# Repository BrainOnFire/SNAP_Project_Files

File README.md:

# S.N.A.P. Version 6.0

</a>

Soil Nutrient Analysis Prototype or S.N.A.P. for short, is an agricultural device that allows farmers to know the best type of nutrient present in a soil sample. The most common types of nutrients found in the ground are Nitrogen, Phosphorus, and Potassium. Photo-sensing sensors can observe these nutrients when an infrared beam hits a sample. Having this information in less than 10 minutes allows the farmer to decide which crop to plant in the selected soil, saving a lot of time and money. The device has come a long way, as this is the sixth iteration of the project. SNAP 6.0 is a BLE, Low-Power, feature-rich sensing device. Here are some specs of the device:

- STM32WB35CCU7A as main MCU (Ultra-low-power dual-core ARM Cortex-M4 with FPU, Bluetooth 5.2, 256KB Flash, 32MHz)
- Integrated Lithium-Ion battery charging with MCP73831 (Charge current 500mA, 4.2V Regulation, Reverse Discharge Protection)
- Battery protection using AP9101C (overcharge voltage, over-discharge voltage, overcharge current, over-discharge current)
- Boost Converter from 3.0V to 5.2V using MT3608 (turns on/off by MCU)
- Temperature and humidity sensing using SHT31-DIS
- OLED Screen for displaying information with low consumption
- PCB Antenna with impedance matching for Bluetooth Low Energy
- USB Type-C 2.0 for 5V power supply and communication

## PCB Design
The design and development of the printed circuit board were done using KiCAD 6.0. The PCB in question is a 4-layer board with a thickness of 1.62 mm and overall dimensions of 66.80 mm x 47.34 mm. The layer stack up is Signal - Ground - Ground - Mixed. 

A USB-C Type Receptacle was used for the power supply coupled with a USBLC6-2SC6 ESD protection chip. Serial Wire is used for the programming of the STM32 chip. A MOSFET and a Schottky Diode are used in order to protect the device when both battery and USB are connected and supply power to the system. Both inputs are regulated by the ADP121 LDO which outputs a voltage of 3.0V to the MCU and to the boost-up converter. The amplification system, the three IR LEDs, the Phototransistor, the SHT31, and the OLED screen are supplied by the 5.2V outputted by the boost-up converter MT3608. Three 2N700 MOSFETs are used to control the IR LEDs through the MCU. 

A total of 27 decoupling capacitors of different values and sizes are used to filter unwanted frequencies. 

A filter PI and RF Band Pass filter are used for the 2.4GHz PCB BLE antenna. The values of capacitance and inductance were calculated using the impedance of the PCB antenna (obtained from [AN5129](https://www.st.com/resource/en/application_note/an5129-low-cost-pcb-antenna-for-24ghz-radio-meander-design-for-stm32wb-series-stmicroelectronics.pdf)), in order to obtain a matching impedance of 50 ohms. The next two images show the first and second pages of the schematic; every part of the device is clearly named.

</a>
</a>

This PCB was manufactured by JLCPCB using the controlled impedance stack up JLC04161H-7628 for a dielectric constant of 4.6. This provides a matching impedance of 50 ohm for the traces of the embedded antenna that mitigate potential power losses due to parasitic capacitances. The SMD components were soldered using an SMD reflow process with a heat gun.

</a>
</a>

Most of the components were selected for the sole purpose of low energy consumption. The battery selected was a 2500mAh LiPo battery which can be charged through the device's USB type C. With this battery capacity, the device is capable of lasting for almost 30 days without charging, while being completely on. If the device's switch is turned OFF, the battery can last for almost a year and a half without the need for charging. Using a special Fluke Ammeter the total consumption of the device in this state is 185nA. This consumption happens because the device is not completely OFF; some components of the battery's charging system and the LDO are still drawing some current. The challenge of this device's design was keeping the consumption to a minimum. The team is very satisfied with the results.

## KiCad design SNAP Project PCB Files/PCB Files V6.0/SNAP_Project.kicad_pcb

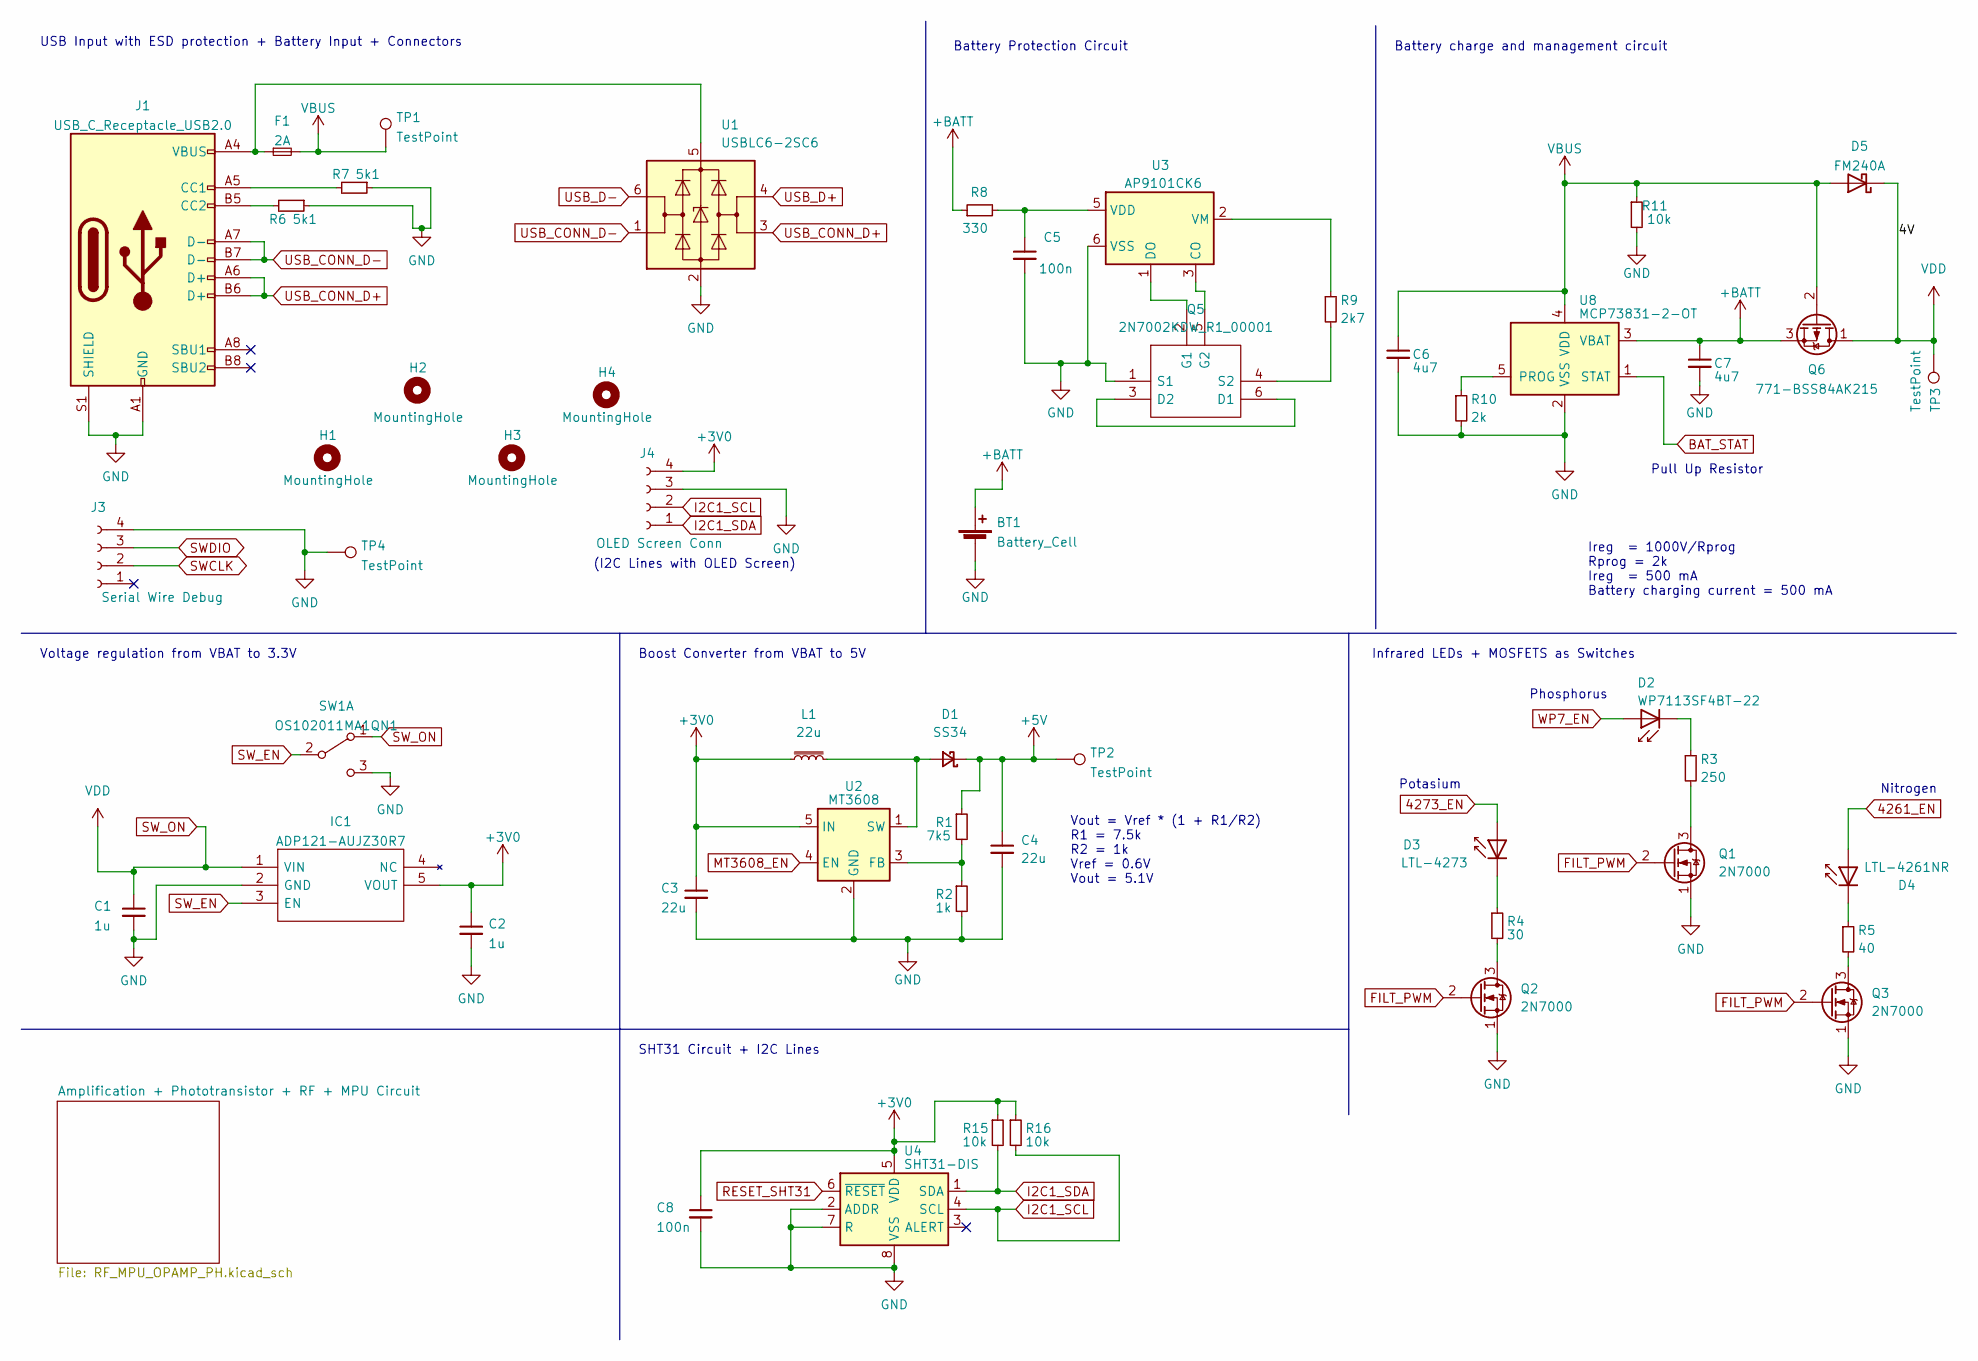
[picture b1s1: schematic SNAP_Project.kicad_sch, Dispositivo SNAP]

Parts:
BT1: Battery_Cell; Molex_KK-254_AE-6410-02A_1x02_P2.54mm_Vertical
C1, C2: 1u; C_1206_3216Metric
C3, C4: 22u; C_1206_3216Metric
C5: 100n; C_1206_3216Metric
C6, C7: 4u7; C_1206_3216Metric
C8: 100n; C_0402_1005Metric
D1: SS34; D_SMC
D2: WP7113SF4BT-22; Molex_KK-254_AE-6410-02A_1x02_P2.54mm_Vertical
D3: LTL-4273; Molex_KK-254_AE-6410-02A_1x02_P2.54mm_Vertical
D4: LTL-4261NR; Molex_KK-254_AE-6410-02A_1x02_P2.54mm_Vertical
D5: FM240A; DIOM5025X231N
F1: 2A; Fuse_0603_1608Metric; Mouser Code MFU0603FF02000P500
H1, H2, H3, H4: MountingHole; MountingHole_3mm_Pad
IC1: ADP121-AUJZ30R7; SOT95P280X100-5N; Mouser Part Number 584-ADP121-AUJZ33R7
J1: USB_C_Receptacle_USB2.0; USB_C_Receptacle_HRO_TYPE-C-31-M-12
J3: Serial Wire Debug; Molex_KK-254_AE-6410-04A_1x04_P2.54mm_Vertical
J4: OLED Screen Conn; Molex_KK-254_AE-6410-04A_1x04_P2.54mm_Vertical
L1: 22u; L_Vishay_IHLP-2020
Q1, Q2, Q3: 2N7000; TO-92_Inline
Q5: 2N7002KDW_R1_00001; SOT65P210X110-6N; Mouser Part Number 241-2N7002KDWR100001
Q6: 771-BSS84AK215; TSOT-23
R1: 7k5; R_1206_3216Metric
R2: 1k; R_1206_3216Metric
R3: 250; R_0805_2012Metric
R4: 30; R_0603_1608Metric
R5: 40; R_0603_1608Metric
R6, R7: 5k1; R_0402_1005Metric
R8: 330; R_0805_2012Metric
R9: 2k7; R_0805_2012Metric
R10: 2k; R_0603_1608Metric
R11: 10k; R_0805_2012Metric
R15, R16: 10k; R_0402_1005Metric
SW1: OS102011MA1QN1
TP1, TP2, TP3, TP4: TestPoint; TestPoint_Pad_D1.0mm
U1: USBLC6-2SC6; SOT-23-6
U2: MT3608; SOT-23-6
U3: AP9101CK6; SOT-23-6
U4: SHT31-DIS; Sensirion_DFN-8-1EP_2.5x2.5mm_P0.5mm_EP1.1x1.7mm
U8: MCP73831-2-OT; SOT-23-5

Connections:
4261_EN: D4.2 (A); also elsewhere on the board
4273_EN: D3.2 (A); also elsewhere on the board
+3V0: C2.1, C3.1, C8.1, IC1.5 (VOUT), J4.4, L1.1, R15.1, R16.1, U2.5 (IN), U4.5 (VDD); also elsewhere on the board
+5V: C4.1, D1.1 (K), R1.1, TP2.1; also elsewhere on the board
+BATT: BT1.1 (+), C7.1, Q6.3 (S), R8.1, U8.3 (VBAT); also elsewhere on the board
BAT_STAT: U8.1 (STAT); also elsewhere on the board
FILT_PWM: Q1.2 (G), Q2.2 (G), Q3.2 (G); also elsewhere on the board
GND: BT1.2 (-), C1.2, C2.2, C3.2, C4.2, C5.2, C6.2, C7.2, C8.2, IC1.2 (GND), J1.A1 (GND), J1.A12 (GND), J1.B1 (GND), J1.B12 (GND), J1.S1 (SHIELD), J3.4, J4.3, Q1.1 (S), Q2.1 (S), Q3.1 (S), Q5.1 (S1), R2.2, R6.1, R7.1, R10.2, R11.2, SW1.3 (C), TP4.1, U1.2 (GND), U2.2 (GND), U3.6 (VSS), U4.2 (ADDR), U4.7 (R), U4.8 (VSS), U4.9 (VSS), U8.2 (VSS); also elsewhere on the board
I2C1_SCL: J4.2, R16.2, U4.4 (SCL); also elsewhere on the board
I2C1_SDA: J4.1, R15.2, U4.1 (SDA); also elsewhere on the board
MT3608_EN: U2.4 (EN); also elsewhere on the board
unnamed: C5.1, R8.2, U3.5 (VDD)
unnamed: D1.2 (A), L1.2, U2.1 (SW)
unnamed: D2.1 (K), R3.1
unnamed: D3.1 (K), R4.1
unnamed: D4.1 (K), R5.1
unnamed: F1.1, J1.A4 (VBUS), J1.A9 (VBUS), J1.B4 (VBUS), J1.B9 (VBUS), U1.5 (VBUS)
unnamed: J1.A5 (CC1), R7.2
unnamed: J1.B5 (CC2), R6.2
unnamed: Q1.3 (D), R3.2
unnamed: Q2.3 (D), R4.2
unnamed: Q3.3 (D), R5.2
unnamed: Q5.2 (G1), U3.1 (DO)
unnamed: Q5.3 (D2), Q5.6 (D1)
unnamed: Q5.4 (S2), R9.2
unnamed: Q5.5 (G2), U3.3 (CO)
unnamed: R1.2, R2.1, U2.3 (FB)
unnamed: R9.1, U3.2 (VM)
unnamed: R10.1, U8.5 (PROG)
RESET_SHT31: U4.6 (~RESET); also elsewhere on the board
SWCLK: J3.2; also elsewhere on the board
SWDIO: J3.3; also elsewhere on the board
SW_EN: IC1.3 (EN), SW1.2 (B)
SW_ON: C1.1, D5.1 (K), IC1.1 (VIN), Q6.1 (D), SW1.1 (A), TP3.1
USB_CONN_D+: J1.A6 (D+), J1.B6 (D+), U1.3 (I/O2)
USB_CONN_D-: J1.A7 (D-), J1.B7 (D-), U1.1 (I/O1)
USB_D+: U1.4 (I/O2); also elsewhere on the board
USB_D-: U1.6 (I/O1); also elsewhere on the board
VBUS: C6.1, D5.2 (A), F1.2, Q6.2 (G), R11.1, TP1.1, U8.4 (VDD)
WP7_EN: D2.2 (A); also elsewhere on the board

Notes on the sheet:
Boost Converter from VBAT to 5V
(I2C Lines with OLED Screen)
Ireg = 1000V/Rprog Rprog = 2k Ireg = 500 mA Battery charging current = 500 mA
Voltage regulation from VBAT to 3.3V
Potasium
Vout = Vref * (1 + R1/R2) R1 = 7.5k R2 = 1k Vref = 0.6V Vout = 5.1V
SHT31 Circuit + I2C Lines
USB Input with ESD protection + Battery Input + Connectors
Phosphorus
Pull Up Resistor
Nitrogen
Battery Protection Circuit
Battery charge and management circuit
Infrared LEDs + MOSFETS as Switches

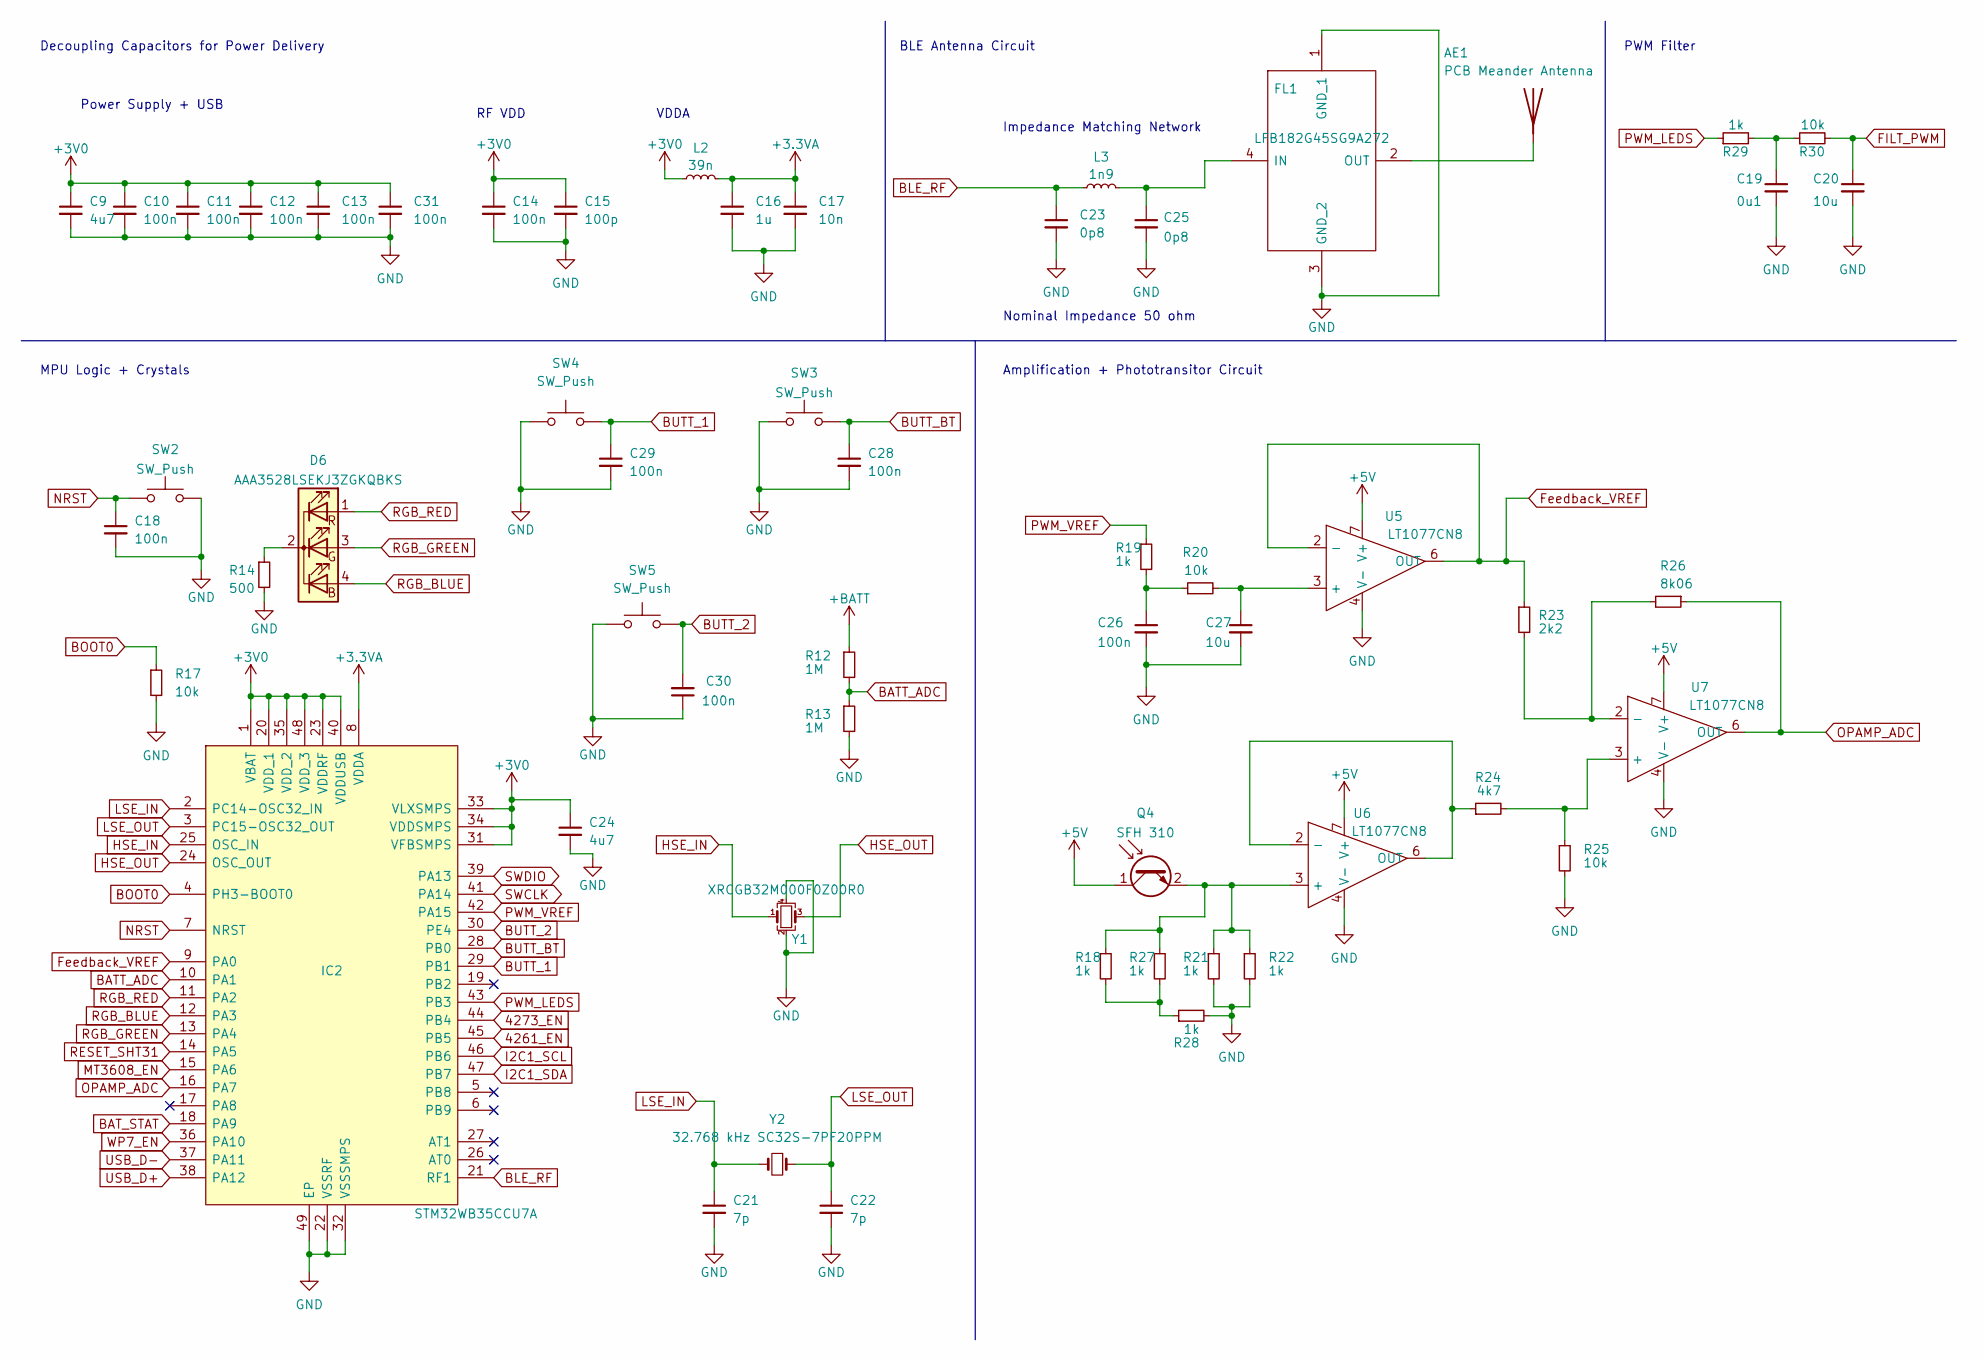
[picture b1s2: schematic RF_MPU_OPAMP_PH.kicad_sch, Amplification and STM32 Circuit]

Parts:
AE1: PCB Meander Antenna
C9, C24: 4u7; C_0402_1005Metric
C10, C11, C12, C13, C14, C26, C31: 100n; C_0402_1005Metric
C15: 100p; C_0402_1005Metric
C16: 1u; C_0402_1005Metric
C17: 10n; C_0402_1005Metric
C18, C28, C29, C30: 100n; C_0402_1005Metric; LCSC Part # C307331
C19: 0u1; C_0402_1005Metric
C20, C27: 10u; C_0402_1005Metric
C21, C22: 7p; C_0402_1005Metric; LCSC Part # C307331
C23, C25: 0p8; C_0402_1005Metric
D6: AAA3528LSEKJ3ZGKQBKS
FL1: LFB182G45SG9A272; Mouser Part Number 81-LFB182G45SG9A272
IC2: STM32WB35CCU7A; QFN50P700X700X65-49N-D; Mouser Part Number 511-STM32WB35CCU7A
L2: 39n; L_0402_1005Metric
L3: 1n9; L_0402_1005Metric
Q4: SFH 310; Molex_KK-254_AE-6410-02A_1x02_P2.54mm_Vertical
R12, R13: 1M; R_0402_1005Metric
R14: 500; R_0603_1608Metric; LCSC Part # C25744
R17: 10k; R_0402_1005Metric; LCSC Part # C25744
R18, R19, R21, R22, R27, R28, R29: 1k; R_0805_2012Metric
R20, R25, R30: 10k; R_0805_2012Metric
R23: 2k2; R_0805_2012Metric
R24: 4k7; R_0805_2012Metric
R26: 8k06; R_0805_2012Metric
SW2: SW_Push; SW_SPST_B3U-1000P; LCSC Part # B3U-1000P
SW3, SW4, SW5: SW_Push; Molex_KK-254_AE-6410-02A_1x02_P2.54mm_Vertical; LCSC Part # B3U-1000P
U5, U6, U7: LT1077CN8; DIP-8_W7.62mm
Y1: XRCGB32M000F0Z00R0
Y2: 32.768 kHz SC32S-7PF20PPM; Crystal_SMD_3215-2Pin_3.2x1.5mm

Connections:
4261_EN: IC2.45 (PB5); also elsewhere on the board
4273_EN: IC2.44 (PB4); also elsewhere on the board
+3.3VA: C16.1, C17.1, IC2.8 (VDDA), L2.2
+3V0: C9.1, C10.1, C11.1, C12.1, C13.1, C14.1, C15.1, C24.1, C31.1, IC2.1 (VBAT), IC2.20 (VDD_1), IC2.23 (VDDRF), IC2.31 (VFBSMPS), IC2.33 (VLXSMPS), IC2.34 (VDDSMPS), IC2.35 (VDD_2), IC2.40 (VDDUSB), IC2.48 (VDD_3), L2.1; also elsewhere on the board
+5V: Q4.1 (C), U5.7 (V+), U6.7 (V+), U7.7 (V+); also elsewhere on the board
+BATT: R12.1; also elsewhere on the board
BATT_ADC: IC2.10 (PA1), R12.2, R13.1
BAT_STAT: IC2.18 (PA9); also elsewhere on the board
BLE_RF: C23.1, IC2.21 (RF1), L3.1
BOOT0: IC2.4 (PH3-BOOT0), R17.1
BUTT_1: C29.1, IC2.29 (PB1), SW4.2
BUTT_2: C30.2, IC2.30 (PE4), SW5.2
BUTT_BT: C28.1, IC2.28 (PB0), SW3.2
FILT_PWM: C20.1, R30.2; also elsewhere on the board
Feedback_VREF: IC2.9 (PA0), R23.1, U5.2 (-), U5.6 (OUT)
GND: C9.2, C10.2, C11.2, C12.2, C13.2, C14.2, C15.2, C16.2, C17.2, C18.2, C19.2, C20.2, C21.2, C22.2, C23.2, C24.2, C25.2, C26.2, C27.2, C28.2, C29.2, C30.1, C31.2, FL1.1 (GND_1), FL1.3 (GND_2), IC2.22 (VSSRF), IC2.32 (VSSSMPS), IC2.49 (EP), R13.2, R14.2, R17.2, R21.2, R22.2, R25.2, R28.2, SW2.2, SW3.1, SW4.1, SW5.1, U5.4 (V-), U6.4 (V-), U7.4 (V-), Y1.2, Y1.4; also elsewhere on the board
HSE_IN: IC2.25 (OSC_IN), Y1.1
HSE_OUT: IC2.24 (OSC_OUT), Y1.3
I2C1_SCL: IC2.46 (PB6); also elsewhere on the board
I2C1_SDA: IC2.47 (PB7); also elsewhere on the board
LSE_IN: C21.1, IC2.2 (PC14-OSC32_IN), Y2.2
LSE_OUT: C22.1, IC2.3 (PC15-OSC32_OUT), Y2.1
MT3608_EN: IC2.15 (PA6); also elsewhere on the board
NRST: C18.1, IC2.7 (NRST), SW2.1
unnamed: AE1.1 (A), FL1.2 (OUT)
unnamed: C19.1, R29.2, R30.1
unnamed: C25.1, FL1.4 (IN), L3.2
unnamed: C26.1, R19.2, R20.1
unnamed: C27.1, R20.2, U5.3 (+)
unnamed: D6.2 (K), R14.1
unnamed: Q4.2 (E), R18.1, R21.1, R22.1, R27.1, U6.3 (+)
unnamed: R18.2, R27.2, R28.1
unnamed: R23.2, R26.2, U7.2 (-)
unnamed: R24.1, U6.2 (-), U6.6 (OUT)
unnamed: R24.2, R25.1, U7.3 (+)
OPAMP_ADC: IC2.16 (PA7), R26.1, U7.6 (OUT)
PWM_LEDS: IC2.43 (PB3), R29.1
PWM_VREF: IC2.42 (PA15), R19.1
RESET_SHT31: IC2.14 (PA5); also elsewhere on the board
RGB_BLUE: D6.4 (BA), IC2.12 (PA3)
RGB_GREEN: D6.3 (GA), IC2.13 (PA4)
RGB_RED: D6.1 (RA), IC2.11 (PA2)
SWCLK: IC2.41 (PA14); also elsewhere on the board
SWDIO: IC2.39 (PA13); also elsewhere on the board
USB_D+: IC2.38 (PA12); also elsewhere on the board
USB_D-: IC2.37 (PA11); also elsewhere on the board
WP7_EN: IC2.36 (PA10); also elsewhere on the board

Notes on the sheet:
Decoupling Capacitors for Power Delivery
BLE Antenna Circuit
Nominal Impedance 50 ohm
RF VDD
PWM Filter
Power Supply + USB
Impedance Matching Network
MPU Logic + Crystals
VDDA
Amplification + Phototransitor Circuit

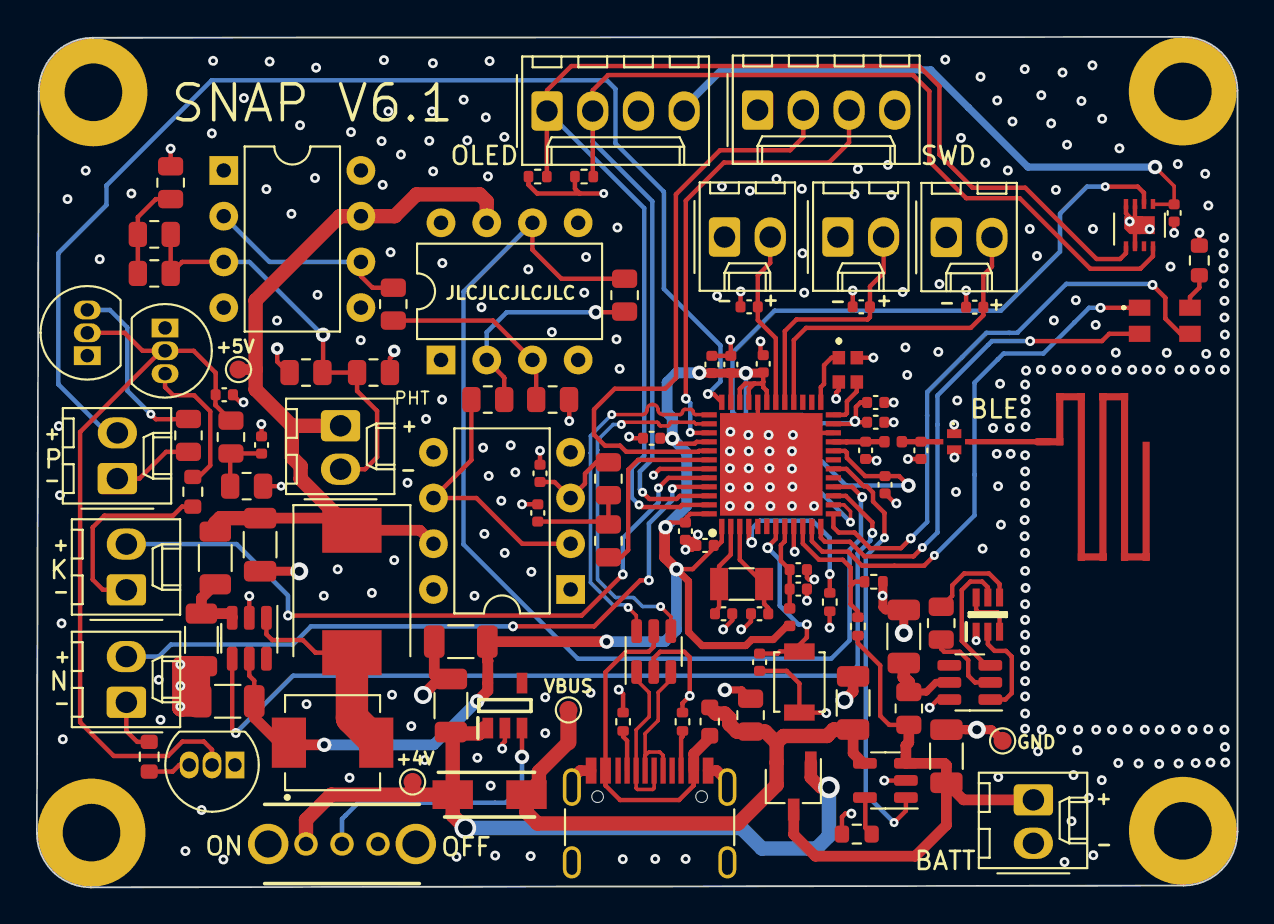
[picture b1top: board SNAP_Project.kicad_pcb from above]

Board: 4 copper layers, 66.7 x 47.2 mm, 108 parts (0 on the bottom side), 70 nets.

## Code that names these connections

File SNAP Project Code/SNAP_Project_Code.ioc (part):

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Mcu.Name=STM32WB35C(C-E)UxA
Mcu.Package=UFQFPN48
Mcu.UserName=STM32WB35CCUxA
PA0.GPIOParameters=GPIO_Label
PA0.GPIO_Label=Feedback_VREF
PA0.Signal=ADCx_IN5
PA1.GPIOParameters=GPIO_Label
PA1.GPIO_Label=BATT_ADC
PA1.Signal=ADCx_IN6
PA10.GPIOParameters=GPIO_Label
PA10.GPIO_Label=LED_WP7_EN
PA10.Signal=GPIO_Output
PA11.Mode=Device
PA11.Signal=USB_DM
PA12.Mode=Device
PA12.Signal=USB_DP
PA13.Mode=Serial_Wire
PA13.Signal=SYS_JTMS-SWDIO
PA14.Mode=Serial_Wire
PA14.Signal=SYS_JTCK-SWCLK
PA15.GPIOParameters=GPIO_Label
PA15.GPIO_Label=PWM_VREF
PA15.Signal=S_TIM2_CH1
PA2.GPIOParameters=GPIO_Label
PA2.GPIO_Label=RGB_RED
PA2.Signal=GPIO_Output
PA3.GPIOParameters=GPIO_Label
PA3.GPIO_Label=RGB_BLUE
PA3.Signal=GPIO_Output
PA4.GPIOParameters=GPIO_Label
PA4.GPIO_Label=RGB_GREEN
PA4.Signal=GPIO_Output
PA5.GPIOParameters=PinState,GPIO_Label
PA5.GPIO_Label=RESET_SHT31
PA5.PinState=GPIO_PIN_SET
PA5.Signal=GPIO_Output
PA6.GPIOParameters=GPIO_Label
PA6.GPIO_Label=MT3608_EN
PA6.Signal=GPIO_Output
PA7.GPIOParameters=GPIO_Label
PA7.GPIO_Label=OPAMP_ADC
PA7.Signal=ADCx_IN12
PA9.GPIOParameters=GPIO_PuPd,GPIO_Label,GPIO_ModeDefaultEXTI
PA9.GPIO_Label=BATT_STAT
PA9.GPIO_ModeDefaultEXTI=GPIO_MODE_IT_RISING
PA9.GPIO_PuPd=GPIO_PULLUP
PA9.Signal=GPXTI9
PB0.GPIOParameters=GPIO_PuPd,GPIO_Label
PB0.GPIO_Label=BUTT_BT
PB0.GPIO_PuPd=GPIO_PULLUP
PB0.Signal=GPIO_Input
PB1.GPIOParameters=GPIO_PuPd,GPIO_Label
PB1.GPIO_Label=BUTT_1
PB1.GPIO_PuPd=GPIO_PULLUP
PB1.Signal=GPIO_Input
PB3.GPIOParameters=GPIO_Label
PB3.GPIO_Label=PWM_LEDS
PB3.Signal=S_TIM2_CH2
PB4.GPIOParameters=GPIO_Label
PB4.GPIO_Label=LED_4273_EN
PB4.Signal=GPIO_Output
PB5.GPIOParameters=GPIO_Label
PB5.GPIO_Label=LED_4261_EN
PB5.Signal=GPIO_Output
PB6.Mode=I2C
PB6.Signal=I2C1_SCL
PB7.Mode=I2C
PB7.Signal=I2C1_SDA
PC14-OSC32_IN.Mode=LSE-External-Oscillator
PC14-OSC32_IN.Signal=RCC_OSC32_IN
PC15-OSC32_OUT.Mode=LSE-External-Oscillator
PC15-OSC32_OUT.Signal=RCC_OSC32_OUT
PE4.GPIOParameters=GPIO_PuPd,GPIO_Label
PE4.GPIO_Label=BUTT_2
PE4.GPIO_PuPd=GPIO_PULLUP
PE4.Signal=GPIO_Input
RCC.HSE_VALUE=32000000
RCC.SYSCLKFreq_VALUE=32000000
RCC.SYSCLKSource=RCC_SYSCLKSOURCE_HSE
board=custom

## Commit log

2023-03-12 Code Upload
2023-03-12 Upload PCB 6.0 Files
2023-03-13 Upload of PCB images
2023-03-13 Fix Button Issue
2023-03-14 Uploaded Images
2023-03-14 4v Line fix
2023-03-15 USB Parity Fix
2023-03-15 USB Fix 2 & 3V line fix
2023-03-17 OLED Screen Fix & Board corrections
2023-03-21 Fixed Screen & ADC issues
2023-03-21 Added Screen Information
2023-03-22 Showing values on screen update
2023-04-12 New changes 1.0
2023-04-22 Updated Connectors, LEDs, filter and STM I/O
2023-04-24 Final Commit V 6.1
2023-04-26 Last Commit before production
2023-07-10 Update in BT Code
2023-07-21 Added documentation for all the files.
2023-07-21 Update README.md
    Added some information about the battery and the consumption
